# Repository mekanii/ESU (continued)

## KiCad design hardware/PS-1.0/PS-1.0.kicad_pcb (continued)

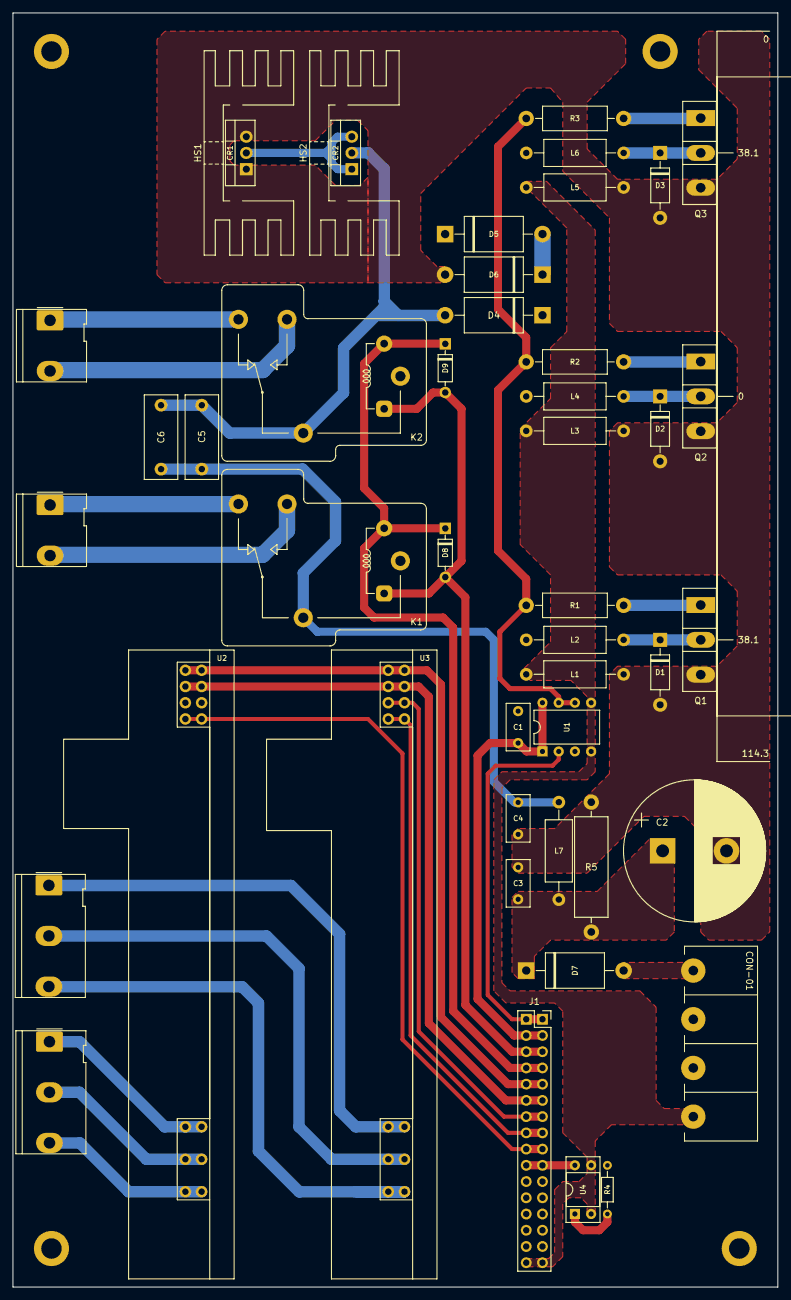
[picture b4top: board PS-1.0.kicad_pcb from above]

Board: 2 copper layers, 119.7 x 199.4 mm, 51 parts (0 on the bottom side), 38 nets.

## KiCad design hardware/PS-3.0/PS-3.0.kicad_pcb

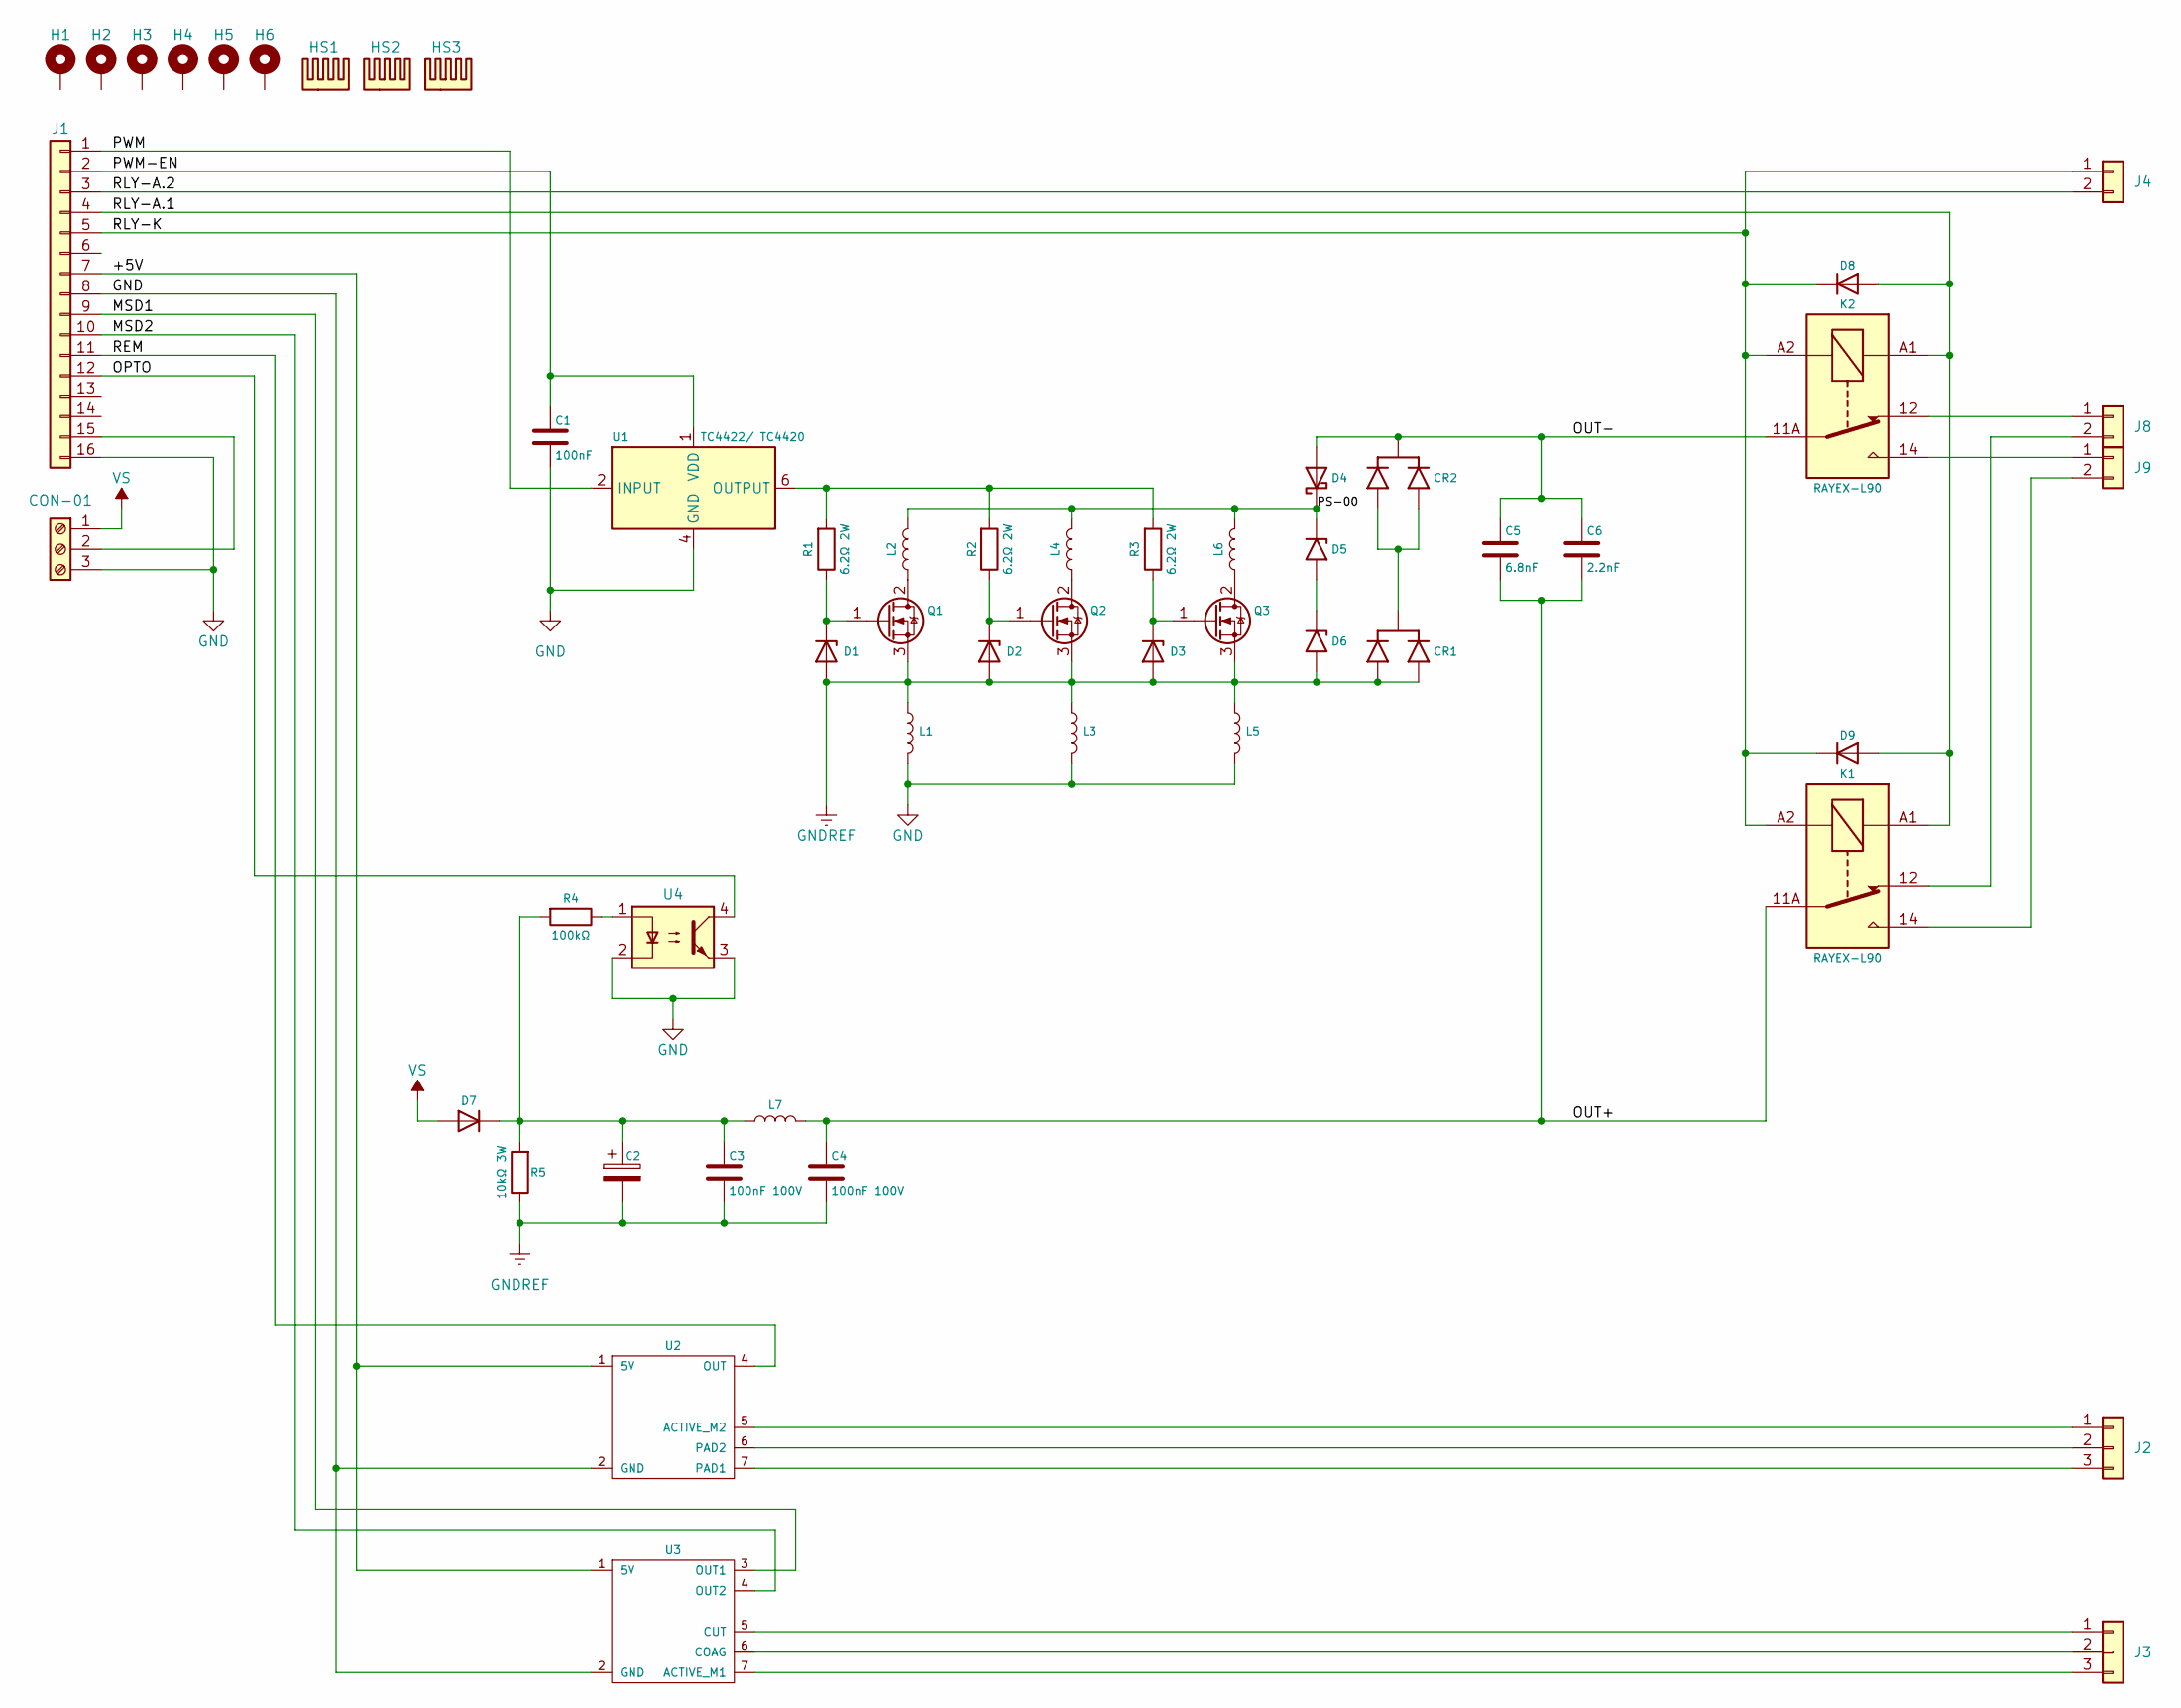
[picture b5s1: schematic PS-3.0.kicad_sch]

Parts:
C1: 100nF; C_Rect_L7.2mm_W3.5mm_P5.00mm_FKS2_FKP2_MKS2_MKP2
C2: 1000µF 160V; CP_Radial_D35.0mm_P10.00mm_SnapIn
C3, C4: 100nF 100V; C_Rect_L7.2mm_W3.5mm_P5.00mm_FKS2_FKP2_MKS2_MKP2
C5: 6.8nF; C_Rect_L13.0mm_W6.0mm_P10.00mm_FKS3_FKP3_MKS4
C6: 2.2nF; C_Rect_L13.0mm_W6.0mm_P10.00mm_FKS3_FKP3_MKS4
CON-01: KF7.62-4; KF7.62-3Pole
CR1, CR2: STTH1002CT; TO-220-3_Vertical
D1, D2, D3: 1N4746A; D_DO-41_SOD81_P10.16mm_Horizontal
D4: SB5H100/ SB5100; D_DO-201AE_P15.24mm_Horizontal
D5, D6: 1.5KE56A; D_DO-201AE_P15.24mm_Horizontal
D7: 10A10; D_DO-201AE_P15.24mm_Horizontal
D8, D9: 1N4148; D_DO-35_SOD27_P7.62mm_Horizontal
H1, H2, H3, H4, H5, H6: MountingHole_Pad; MountingHole_3.2mm_M3_ISO14580_Pad
HS1, HS2: Heatsink; Heatsink_Stonecold_HS-132_32x14mm_2xFixation1.5mm_NoPad
HS3: Heatsink; Heatsink_Custom_10x18x50
J1: PinSocket_02x16_P2.54mm_Vertical; PinSocket_1x16_P2.54mm_Vertical_2
J2, J3: Conn_01x05; Molex_KK-396_5273-05A_1x05_P3.96mm_Vertical_2
J4: Conn_01x02; Molex_KK-396_5273-02A_1x02_P3.96mm_Vertical
J8, J9: Conn_01x02; Molex_KK-396_5273-03A_1x03_P3.96mm_Vertical_2
K1, K2: RAYEX-L90; Relay_SPDT_RAYEX-L90
L1, L2, L3, L4, L5, L6, L7: L; L_Axial_L9.5mm_D4.0mm_P15.24mm_Horizontal_Fastron_SMCC
Q1, Q2, Q3: IRFPE50; TO-247-3_Vertical
R1, R2, R3: 6.2Ω 2W; R_Axial_DIN0411_L9.9mm_D3.6mm_P15.24mm_Horizontal
R4: 100kΩ; R_Axial_DIN0204_L3.6mm_D1.6mm_P7.62mm_Horizontal
R5: 10kΩ 3W; R_Axial_DIN0516_L15.5mm_D5.0mm_P20.32mm_Horizontal
U1: TC4422/ TC4420; DIP-8_W7.62mm
U2: ESU-REM-4.0
U3: ESU-MSD-1.0
U4: PC817; DIP-4_W7.62mm_Socket

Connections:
/+5V: J1.7, U2.1 (5V), U3.1 (5V)
/MSD1: J1.9, U3.3 (OUT1)
/MSD2: J1.10, U3.4 (OUT2)
/OPTO: J1.12, U4.4
/OUT+: C4.1, C5.2, C6.2, K1.11A, K1.11B, L7.2
/OUT-: C5.1, C6.1, CR2.2, D4.2 (A), K2.11A, K2.11B
/PS-00: D4.1 (K), D5.1 (A1), L2.2, L4.2, L6.2
/PWM: J1.1, U1.2 (INPUT)
/PWM-EN: C1.1, J1.2, U1.1 (VDD), U1.8 (VDD)
/REM: J1.11, U2.4 (OUT)
/RLY-A.1: D8.2 (A), D9.2 (A), J1.4, K1.A1, K2.A1
/RLY-A.2: J1.3, J4.2
/RLY-K: D8.1 (K), D9.1 (K), J1.5, J4.1, K1.A2, K2.A2
GND: C1.2, CON-01.3, J1.8, J1.16, L1.2, L3.2, L5.2, U1.4 (GND), U1.5 (GND), U2.2 (GND), U3.2 (GND), U4.2, U4.3
GNDREF: C2.2, C3.2, C4.2, CR1.1, CR1.3, D1.2 (A), D2.2 (A), D3.2 (A), D6.2 (A2), L1.1, L3.1, L5.1, Q1.3 (S), Q2.3 (S), Q3.3 (S), R5.1
unnamed: CON-01.2, J1.15
unnamed: CR1.2, CR2.1, CR2.3
unnamed: D1.1 (K), Q1.1 (G), R1.1
unnamed: D2.1 (K), Q2.1 (G), R2.1
unnamed: D3.1 (K), Q3.1 (G), R3.1
unnamed: D5.2 (A2), D6.1 (A1)
unnamed: C2.1, C3.1, D7.1 (K), L7.1, R4.2, R5.2
unnamed: J2.1, U2.5 (ACTIVE_M2)
unnamed: J2.2, U2.6 (PAD2)
unnamed: J2.3, U2.7 (PAD1)
unnamed: J3.1, U3.5 (CUT)
unnamed: J3.2, U3.6 (COAG)
unnamed: J3.3, U3.7 (ACTIVE_M1)
unnamed: J8.1, K2.12
unnamed: J8.2, K1.12
unnamed: J9.1, K2.14
unnamed: J9.2, K1.14
unnamed: L2.1, Q1.2 (D)
unnamed: L4.1, Q2.2 (D)
unnamed: L6.1, Q3.2 (D)
unnamed: R1.2, R2.2, R3.2, U1.6 (OUTPUT), U1.7 (OUTPUT)
unnamed: R4.1, U4.1
VS: CON-01.1, D7.2 (A)

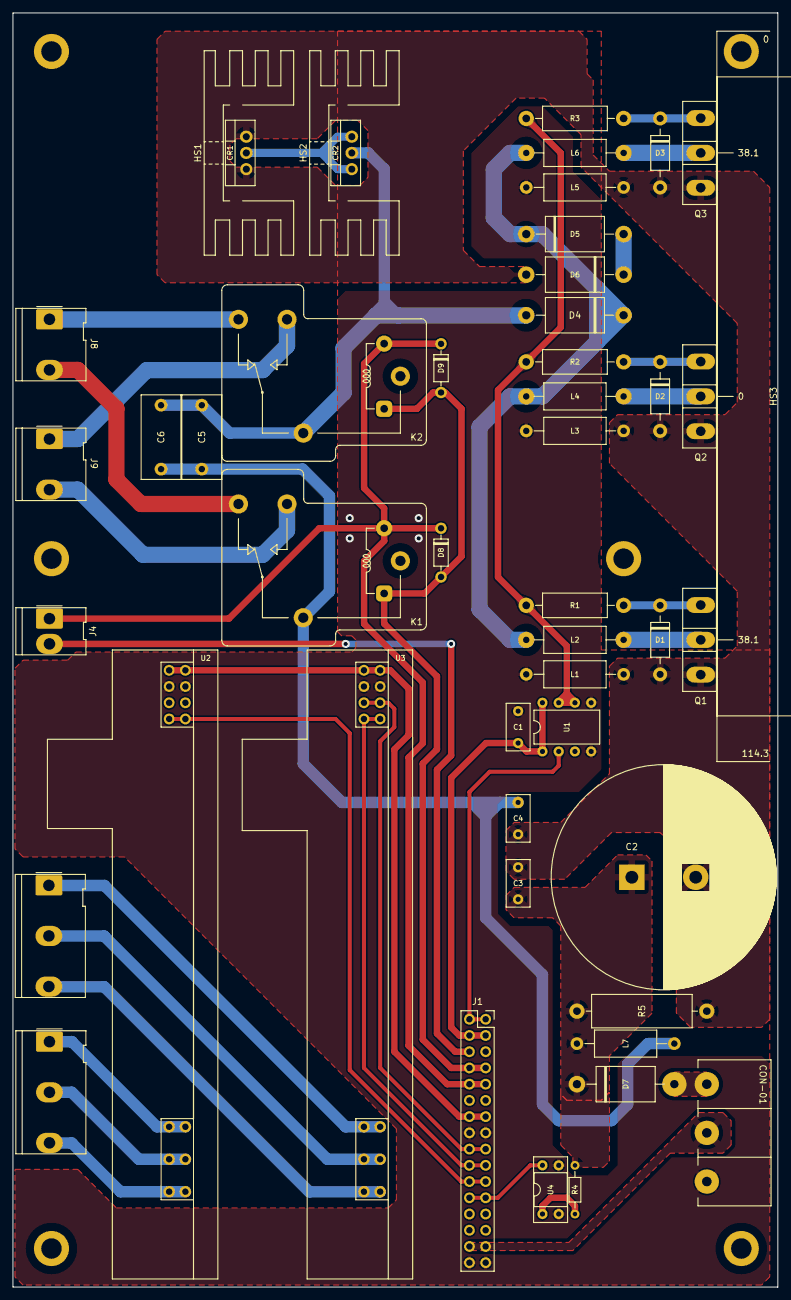
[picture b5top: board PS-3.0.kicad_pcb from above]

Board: 2 copper layers, 119.7 x 199.4 mm, 54 parts (0 on the bottom side), 38 nets.
